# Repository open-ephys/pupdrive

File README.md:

# pupdrive

An ultra low torque drive for tetrode recordings in pups and other small animals

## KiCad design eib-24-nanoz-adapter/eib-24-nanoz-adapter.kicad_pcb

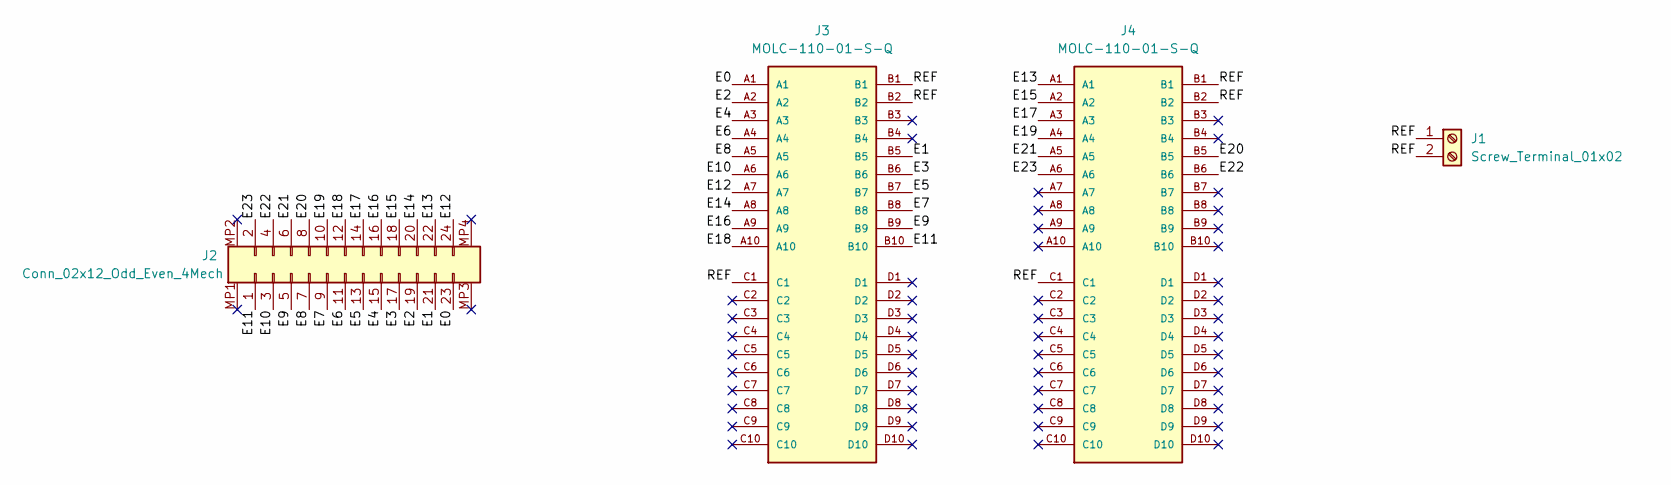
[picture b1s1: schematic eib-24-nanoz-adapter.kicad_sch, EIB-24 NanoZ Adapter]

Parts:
J1: Screw_Terminal_01x02; TerminalBlock_TE_282834-2_1x02_P2.54mm_Horizontal
J2: Conn_02x12_Odd_Even_4Mech; MOLEX_5050662422-5052702412
J3, J4: MOLC-110-01-S-Q; SAMTEC_MOLC-110-01-S-Q

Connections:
/E0: J2.23, J3.A1
/E1: J2.21, J3.B5
/E2: J2.19, J3.A2
/E3: J2.17, J3.B6
/E4: J2.15, J3.A3
/E5: J2.13, J3.B7
/E6: J2.11, J3.A4
/E7: J2.9, J3.B8
/E8: J2.7, J3.A5
/E9: J2.5, J3.B9
/E10: J2.3, J3.A6
/E11: J2.1, J3.B10
/E12: J2.24, J3.A7
/E13: J2.22, J4.A1
/E14: J2.20, J3.A8
/E15: J2.18, J4.A2
/E16: J2.16, J3.A9
/E17: J2.14, J4.A3
/E18: J2.12, J3.A10
/E19: J2.10, J4.A4
/E20: J2.8, J4.B5
/E21: J2.6, J4.A5
/E22: J2.4, J4.B6
/E23: J2.2, J4.A6
/REF: J1.1, J1.2, J3.B1, J3.B2, J3.C1, J4.B1, J4.B2, J4.C1

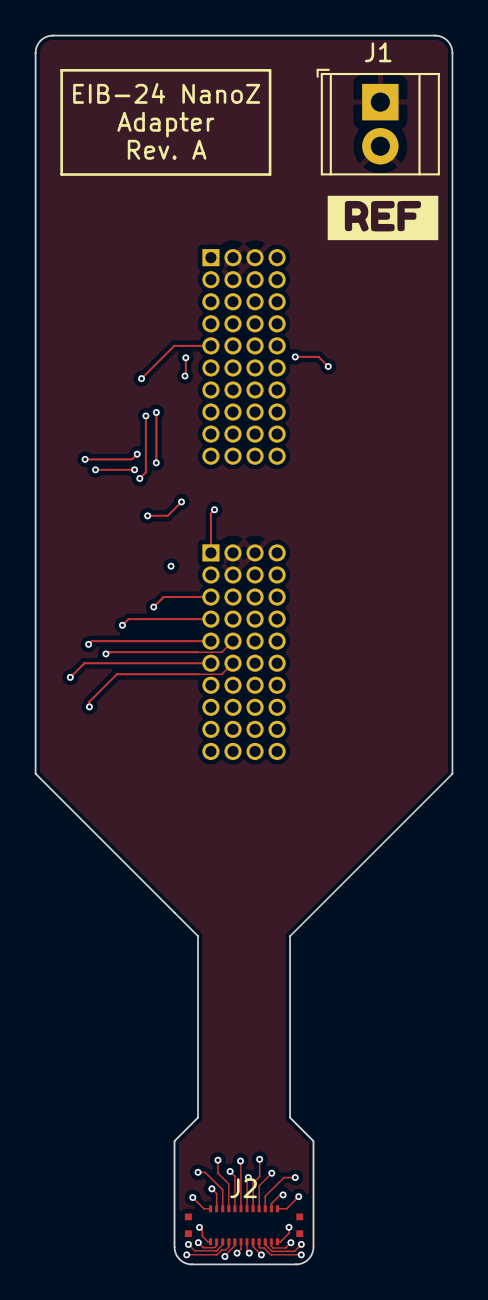
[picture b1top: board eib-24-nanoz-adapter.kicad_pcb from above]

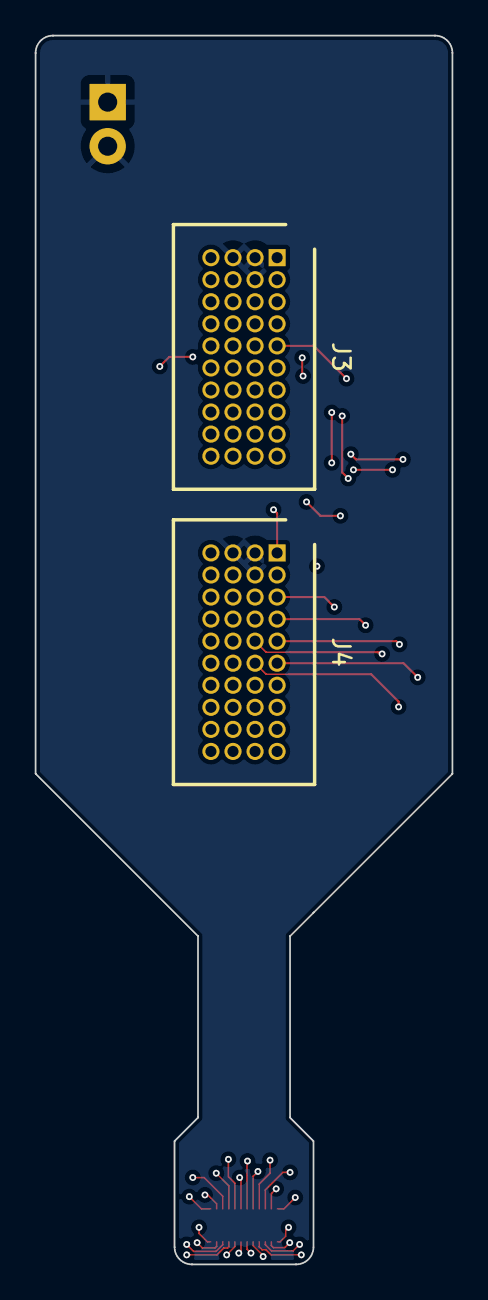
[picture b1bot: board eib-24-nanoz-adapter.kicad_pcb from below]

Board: 4 copper layers, 24.0 x 70.8 mm, 5 parts (2 on the bottom side), 25 nets.

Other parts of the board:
kibuzzard-62F6D4CD: G***; kibuzzard-62F6D4CD

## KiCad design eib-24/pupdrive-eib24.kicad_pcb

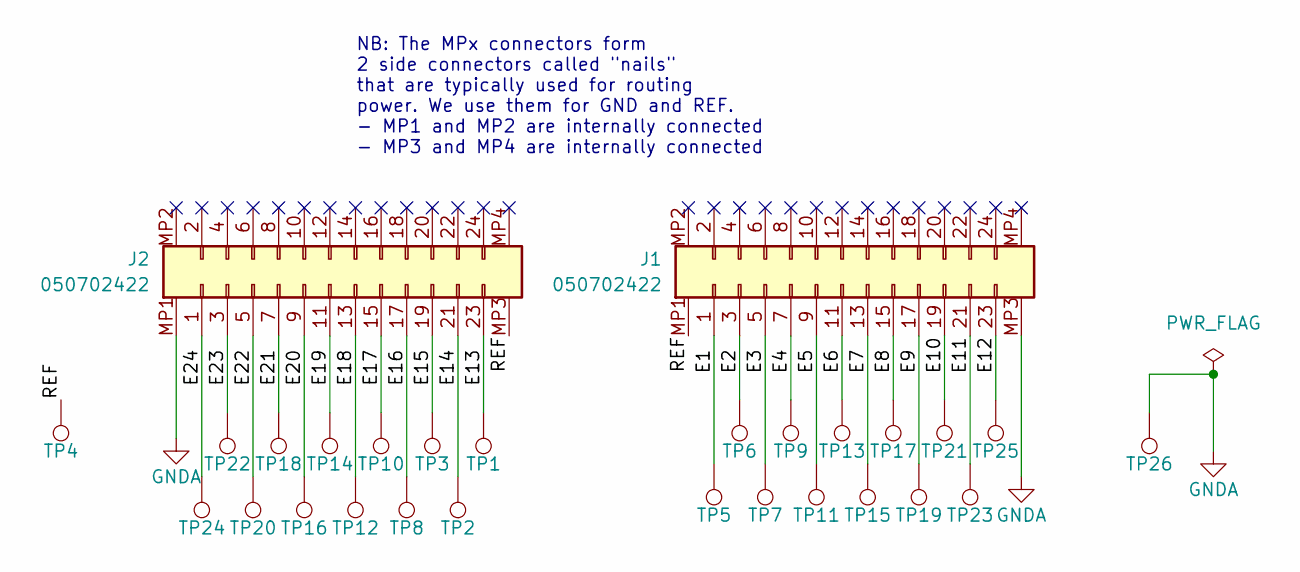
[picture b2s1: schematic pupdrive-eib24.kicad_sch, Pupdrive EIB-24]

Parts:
J1, J2: 050702422; MOLEX_5050702422
TP1, TP2, TP3, TP4, TP5, TP6, TP7, TP8, TP9, TP10, TP11, TP12, TP13, TP14, TP15, TP16, TP17, TP18, TP19, TP20, TP21, TP22, TP23, TP24, TP25, TP26: TestPoint; NEURALYNX_SMALL-GOLD-PIN

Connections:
/E1: J1.1, TP5.1
/E2: J1.3, TP6.1
/E3: J1.5, TP7.1
/E4: J1.7, TP9.1
/E5: J1.9, TP11.1
/E6: J1.11, TP13.1
/E7: J1.13, TP15.1
/E8: J1.15, TP17.1
/E9: J1.17, TP19.1
/E10: J1.19, TP21.1
/E11: J1.21, TP23.1
/E12: J1.23, TP25.1
/E13: J2.23, TP1.1
/E14: J2.21, TP2.1
/E15: J2.19, TP3.1
/E16: J2.17, TP8.1
/E17: J2.15, TP10.1
/E18: J2.13, TP12.1
/E19: J2.11, TP14.1
/E20: J2.9, TP16.1
/E21: J2.7, TP18.1
/E22: J2.5, TP20.1
/E23: J2.3, TP22.1
/E24: J2.1, TP24.1
/REF: J1.MP1 (MountPin1), J2.MP3 (MountPin3), TP4.1
GNDA: J1.MP3 (MountPin3), J2.MP1 (MountPin1), TP26.1

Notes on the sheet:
NB: The MPx connectors form 2 side connectors called "nails" that are typically used for routing power. We use them for GND and REF. - MP1 and MP2 are internally connected - MP3 and MP4 are internally connected

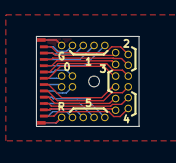
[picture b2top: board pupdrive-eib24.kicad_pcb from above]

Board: 2 copper layers, 5.7 x 5.0 mm, 28 parts (1 on the bottom side), 26 nets.

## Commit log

2021-11-11 Initial commit base design
2022-01-26 Cleaned up design for intial print test
    - Scaled to fit current EIB design
    - Added stabilizer features on hinge so it bends at bottom
    - Made 3 variants for print test (STLs)
2022-01-26 Added variant with free(er) sides to accommodate more gold pins
2022-01-26 Create 24-pin EIB
    - Uses latest slim stack connector
    - Semimanual creation of solidworks model
2022-01-26 Fend off git misuse
2022-01-28 Made a new more parameterizable flexure
    - Worked off of jakobs designs
    - Model of complete assembly with room for pins
2022-02-21 First prototype sent to printers
    - We will need to make the base smaller but its important to test the
    bellow first to see if we need to return to square one.
2022-03-25 Archive work before moving to leaf-spring design
2022-03-25 Make eib-24 smaller to fit leaf-spring drive
2022-03-26 Flex connector and eib-24 complete
    - I need to panelize these and make different variants of the flex
    connector with different lengths.
2022-03-28 Pupdrive EIB-24 and Flex-24 for initial fabrication
2022-03-28 Clean up mechanical parts
    - Leaf spring sent to protolabs for fabrication
2022-03-30 Made drive and eib holders
    - These are comptible with the existing mouse drive assembly jig
2022-03-30 Forgot to add leaf-spring STL
    - Changes requested by protolabs
2022-08-05 Pupdrive revision A
    - This is the first revision of the pupdrive, ready for real-world
    testing
    - Lots of changes informed by real-world testing.
    - There is virtually no assembly documentation. This will be added
    following in-the-field verification
2022-08-14 EIB-24 NanoZ Adapter Rev. A
    - In production
    - E0-23 on the EIB map to E0-23 on the NanoZ.
2022-11-29 Changes following first real-world test
    - EIB revision B that allows it to be screwed into EIB holder for
    assembly
    - Small changes to drive design
